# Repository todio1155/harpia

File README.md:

# HARPIA NINHO: introdução

Projeto "Harpia Ninho" é uma impressora 3D projetada para ser open-source (leia a licença atual do projeto antes de usar), durável, modificável e atualmente ficando mais fácil de consertar e fazer módulos de expansão, tipo um LAN/Ethernet, mais NTC, driver de passo, FRAM e muito mais. Ele foi feito para ATX-20 ou ATX-24; licença "CERN-OHL-S-2.0".
## contexto
Eu queria uma impressora 3D barata, eficiente, personalizada e open-source que pudesse ser muito modificada. 

## pré requisitos
[kicad 10.0 ou maior](https://www.kicad.org/download/)

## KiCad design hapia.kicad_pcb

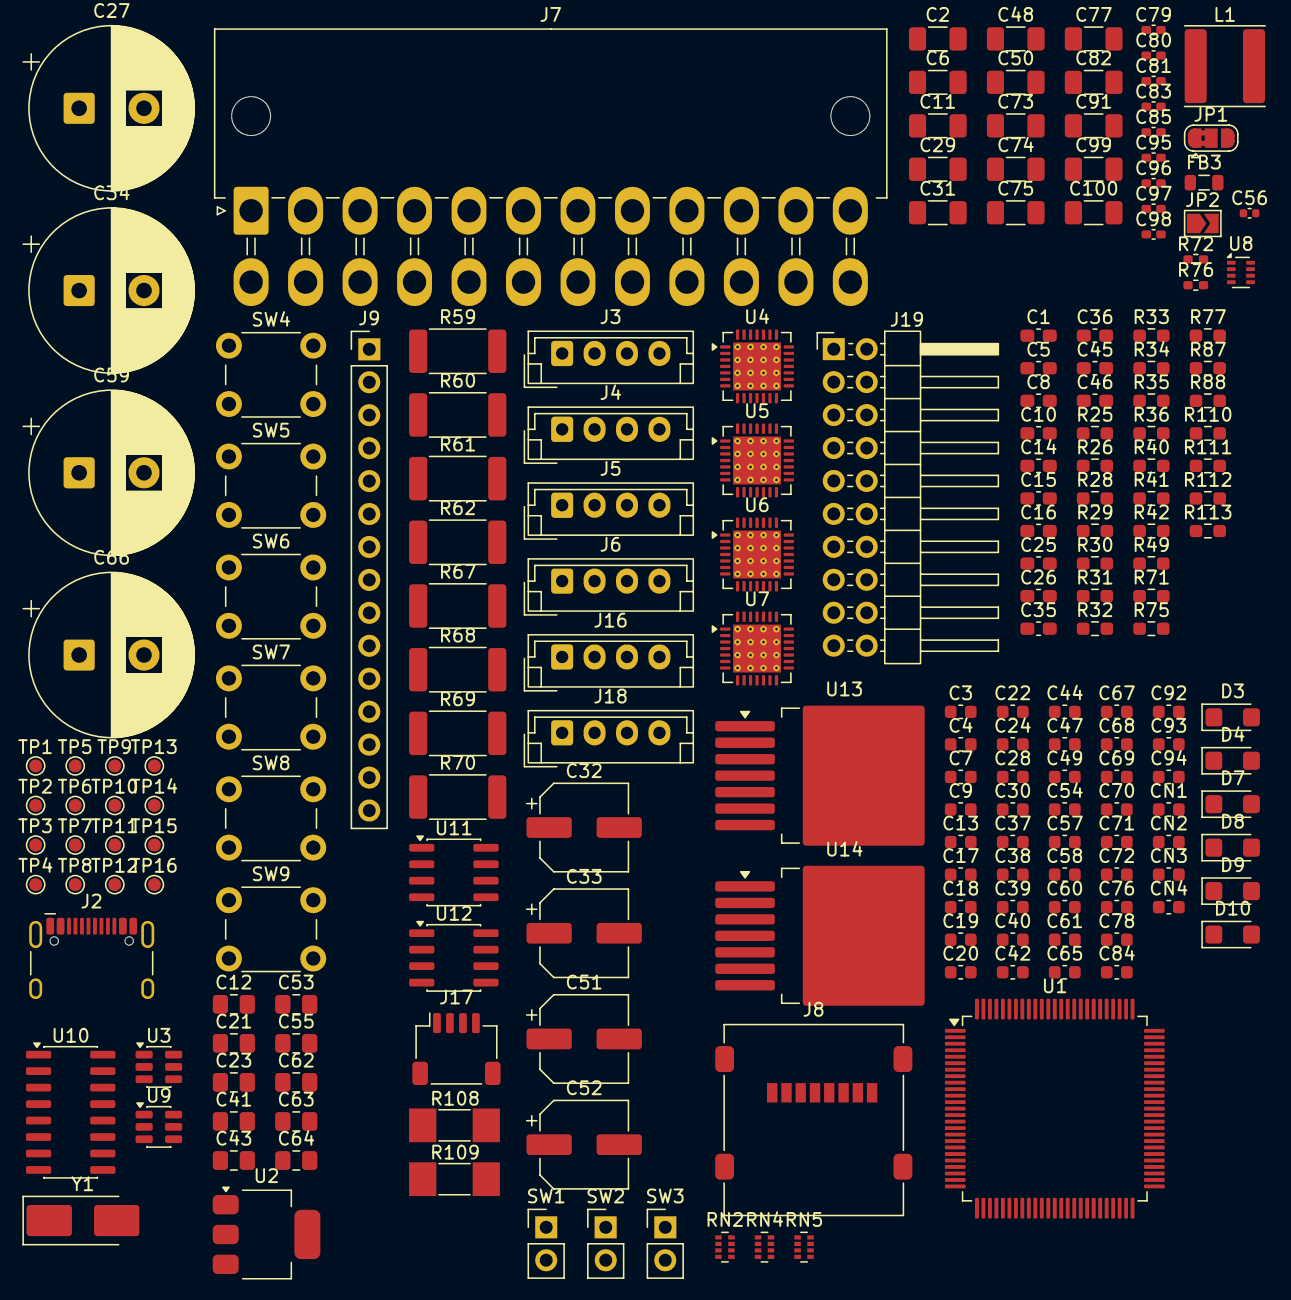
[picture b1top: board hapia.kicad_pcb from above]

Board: 6 copper layers, 200 parts (0 on the bottom side), 149 nets, no tracks yet.

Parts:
C1, C5: 22pf; C_0603_1608Metric_Pad1.08x0.95mm_HandSolder
C2, C6, C11, C29, C31, C48, C50, C73, C74, C75, C77, C82, C91, C99, C100: 10µf; C_1206_3216Metric_Pad1.33x1.80mm_HandSolder
C3, C4, C7, C9, C13, C17, C18, C19, C20, C22, C24, C28, C30, C37, C38, C39, C40, C42, C44, C47, C49, C54, C57, C58, C60, C61, C65, C67, C68, C69, C70, C71, C72, C76, C78, C84, C92, C93, C94: 100nf; C_0603_1608Metric
C8, C10, C14, C25, C26, C45, C46: 4.7µf; C_0603_1608Metric_Pad1.08x0.95mm_HandSolder
C12, C21, C23, C41, C43, C63: 1µf; C_0805_2012Metric_Pad1.18x1.45mm_HandSolder
C15, C16, C35, C36: 22nf; C_0603_1608Metric_Pad1.08x0.95mm_HandSolder
C27, C34, C59, C66: 1000µf; CP_Radial_D12.5mm_P5.00mm
C32, C33, C51, C52: 100µf; CP_Elec_6.3x7.7
C53, C55, C62, C64: 22µf; C_0805_2012Metric_Pad1.18x1.45mm_HandSolder
C56: 33nf; C_0402_1005Metric
C79, C80, C81, C83, C85, C95, C96, C97, C98: 10nf; C_0402_1005Metric_Pad0.74x0.62mm_HandSolder
CN1, CN2, CN3, CN4: 100nf; C_0603_1608Metric
D3: SMF5V0A; D_SMF
D4, D7, D8, D9: SMF3.3; D_SMF
D10: SMF12A; D_SMF
FB3: FerriteBead; L_0805_2012Metric
J2: USB_C_Receptacle_USB2.0_16P; USB_C_Receptacle_HCTL_HC-TYPE-C-16P-01A
J3, J4, J5, J6, J16, J18: Conn_01x04_Pin; JST_EH_B4B-EH-A_1x04_P2.50mm_Vertical
J7: ATX-24; Molex_Mini-Fit_Jr_5569-24A2_2x12_P4.20mm_Horizontal
J8: Micro_SD_Card; microSD_HC_Molex_47219-2001
J9: Conn_01x15_Pin; PinHeader_1x15_P2.54mm_Vertical
J17: Conn_01x04_MountingPin; JST_SH_SM04B-SRSS-TB_1x04-1MP_P1.00mm_Horizontal
J19: ETH; PinHeader_2x10_P2.54mm_Horizontal
JP1: usb/atx; SolderJumper-3_P1.3mm_Bridged2Bar12_RoundedPad1.0x1.5mm
JP2: fre; SolderJumper-2_P1.3mm_Open_TrianglePad1.0x1.5mm
L1: 4.7µh; L_Changjiang_FNR6020S
R25, R26: 22Ω; R_0603_1608Metric_Pad0.98x0.95mm_HandSolder
R28, R29, R30, R31, R32, R33, R34, R35, R36, R40, R41, R42, R49, R75, R110, R111, R112, R113: 33Ω; R_0603_1608Metric_Pad0.98x0.95mm_HandSolder
R59, R60, R61, R62, R67, R68, R69, R70: 100mΩ; R_2512_6332Metric_Pad1.40x3.35mm_HandSolder
R71: 100kΩ; R_0603_1608Metric_Pad0.98x0.95mm_HandSolder
R72: 57.6kΩ; R_0402_1005Metric_Pad0.72x0.64mm_HandSolder
R76: 330Ω; R_0402_1005Metric_Pad0.72x0.64mm_HandSolder
R77: 30.9kΩ; R_0603_1608Metric_Pad0.98x0.95mm_HandSolder
R87, R88: 4.7kΩ; R_0603_1608Metric_Pad0.98x0.95mm_HandSolder
R108, R109: 12Ω; R_MELF_MMB-0207
RN2, RN4, RN5: 33Ω; R_Array_Concave_4x0402
SW1, SW2, SW3: SW_Push; PinHeader_1x02_P2.54mm_Vertical
SW4, SW5, SW6, SW7, SW8, SW9: SW_P; SW_PUSH_6mm_H5mm
TP1, TP2, TP4, TP13: TestPoint; TestPoint_Pad_D1.0mm
TP3, TP16: 3.3v; TestPoint_Pad_D1.0mm
TP5, TP6, TP9, TP10: 3.3v_power; TestPoint_Pad_D1.0mm
TP7, TP8, TP11, TP12: 12v_power; TestPoint_Pad_D1.0mm
TP14: 12v; TestPoint_Pad_D1.0mm
TP15: 5v; TestPoint_Pad_D1.0mm
U1: STM32F407VET6; LQFP-100_14x14mm_P0.5mm
U2: AMS1117-3.3; SOT-223-3_TabPin2
U3, U9: SRV05-4HTG-D; SOT-23-6
U4, U5, U6, U7: TMC2209-LA; VQFN-28-1EP_5x5mm_P0.5mm_EP3.7x3.7mm_ThermalVias
U8: TPS62933F; SOT-583-8
U10: 74HC4051; SOIC-16_3.9x9.9mm_P1.27mm
U11, U12: UCC27524DR; SOIC-8_3.9x4.9mm_P1.27mm
U13, U14: IRFS7530TRL7PP; TO-263-7_TabPin4
Y1: 8mhz; Crystal_SMD_5032-2Pin_5.0x3.2mm_HandSoldering

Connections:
3.3v/1: C2.1, CN1.1 (common), CN1.2 (C1), CN2.2 (C1), JP1.2 (C), TP3.1 (1_1), U1.6 (VBAT), U1.11 (VDD), U1.19 (VDD), U1.28 (VDD), U1.50 (VDD), U1.75 (VDD), U1.100 (VDD)
+3.3V: C61.1, C62.1, C64.1, C70.1, C73.1, C76.1, C77.1, C78.1, C82.1, C91.1, C92.2, D4.1 (A1), J8.4 (VDD), J16.1, J17.1, J18.1, JP1.3 (B), L1.2, R76.1, R87.1, R88.1, SW4.2, SW5.2, SW6.2, SW7.2, SW8.2, SW9.2, TP16.1 (1_1), U9.2 (VN), U10.16 (VCC), U11.6 (V_{DD}), U12.6 (V_{DD})
+3.3Vdev: C12.1, D9.1 (A1), JP1.1 (A), U2.2 (VO)
+3V3: C13.1, C14.1, C19.2, C20.2, C21.2, C23.2, C38.2, C40.2, C41.2, C43.2, TP5.1 (1_1), TP6.1 (1_1), TP9.1 (1_1), TP10.1 (1_1), U4.15 (VCC_IO), U5.9 (MS1/AD0), U5.15 (VCC_IO), U6.10 (MS2/AD1), U6.15 (VCC_IO), U7.9 (MS1/AD0), U7.10 (MS2/AD1), U7.15 (VCC_IO)
+5V: C60.1, C63.1, C71.1, C74.1, J9.13, TP15.1 (1_1)
+5VSB: C57.1, FB3.2, J9.2
+5Vusb: C11.1, U2.3 (VI)
+12P: C18.1, C28.2, C29.2, C30.2, C31.2, C32.1, C33.1, C47.2, C48.2, C49.2, C50.2, C51.1, C52.1, TP7.1 (1_1), TP8.1 (1_1), TP11.1 (1_1), TP12.1 (1_1), U4.22 (VS), U4.28 (VS), U5.22 (VS), U5.28 (VS), U6.22 (VS), U6.28 (VS), U7.22 (VS), U7.28 (VS)
+12V: C27.1, C34.1, C59.1, C65.1, C66.1, C67.1, C68.1, C69.1, C72.1, C75.1, D10.1 (A1), J9.15, TP14.1 (1_1), U11.2 (INA), U11.4 (INB), U12.2 (INA), U12.4 (INB)
/RMII_expansão/vcc_RMII: C99.1, C100.1, CN3.1 (common), CN3.2 (C1), D7.1 (A1)
ATX_PWR_o: D8.1 (A1), U1.97 (PE0)
CLK_0: C1.1, U1.12 (PH0), Y1.2
CLK_X: C5.1, U1.13 (PH1), Y1.1
Fan_1: U1.46 (PE15), U11.1 (ENA)
Fan_2: U1.43 (PE12), U11.8 (ENB)
GND: C1.2, C2.2, C3.2, C4.2, C5.2, C6.2, C7.2, C8.2, C9.2, C10.2, C11.2, C12.2, C13.2, C14.2, C17.1, C19.1, C20.1, C21.1, C22.1, C23.1, C24.1, C25.1, C26.1, C27.2, C28.1, C29.1, C30.1, C31.1, C32.2, C33.2, C34.2, C37.1, C38.1, C39.1, C40.1, C41.1, C42.1, C43.1, C44.1, C45.1, C46.1, C47.1, C48.1, C49.1, C50.1, C51.2, C52.2, C53.2, C54.2, C55.2, C56.2, C57.2, C59.2, C60.2, C61.2, C62.2, C63.2, C64.2, C65.2, C66.2, C67.2, C70.2, C71.2, C72.2, C73.2, C74.2, C75.2, C76.2, C77.2, C78.2, C79.2, C80.2, C81.2, C82.2, C83.2, C84.2, C85.2, C91.2, C92.1, C93.2, C94.2, C95.2, C96.2, C97.2, C98.2, C99.2, C100.2, D3.2 (A2), D4.2 (A2), D7.2 (A2), D8.2 (A2), D9.2 (A2), D10.2 (A2), J2.A1 (GND), J2.A12 (GND), J2.B1 (GND), J2.B12 (GND), J7.3 (GND), J7.5 (GND), J7.7 (GND), J7.15 (GND), J7.17 (GND), J7.18 (GND), J7.19 (GND), J7.24 (GND), J9.1, J9.3, J9.12, J16.2, J17.2, J17.MP (MountPin), J18.2, JP2.1 (A), R59.2, R60.2, R61.2, R62.2, R67.2, R68.2, R69.2, R70.2, R72.2, SW1.1, SW2.1, SW3.2, U1.10 (VSS), U1.20 (VSSA), U1.27 (VSS), U1.74 (VSS), U1.99 (VSS), U2.1 (GND), U3.5 (VP), U4.3 (GND), U4.9 (MS1/AD0), U4.10 (MS2/AD1), U4.13 (CLK), U4.18 (GND), U4.20 (STDBY), U4.29 (GND), U5.3 (GND), U5.10 (MS2/AD1), U5.13 (CLK), U5.18 (GND), U5.20 (STDBY), U5.29 (GND), U6.3 (GND), U6.9 (MS1/AD0), U6.13 (CLK), U6.18 (GND), U6.20 (STDBY), U6.29 (GND), U7.3 (GND), U7.13 (CLK), U7.18 (GND), U7.20 (STDBY), U7.29 (GND), U8.4 (GND), U9.5 (VP), U10.7 (VEE), U10.8 (GND), U11.3 (GND), U12.3 (GND), U13.2 (S), U13.3 (S), U13.5 (S), U13.6 (S), U13.7 (S), U14.2 (S), U14.3 (S), U14.5 (S), U14.6 (S), U14.7 (S)
MUX_EN: U1.98 (PE1), U10.6 (~E)
NTC_EX: C79.1, U10.13 (A0)
NTC_MUX_0: U1.3 (PE4), U10.11 (S0)
NTC_MUX_1: U1.4 (PE5), U10.10 (S1)
NTC_MUX_2: U1.5 (PE6), U10.9 (S2)
NTC_MUX_out: U1.15 (PC0), U10.3 (A)
NTC_driver_1: C81.1, U10.1 (A4)
NTC_driver_2: C96.1, U10.5 (A5)
NTC_driver_3: C97.1, U10.2 (A6)
NTC_driver_4: C98.1, U10.4 (A7)
NTC_ht: C80.1, U10.14 (A1)
NTC_mosfet_1: C83.1, U10.15 (A2)
NTC_mosfet_2: C95.1, U10.12 (A3)
unnamed: J2.A4 (VBUS), J2.A9 (VBUS), J2.B4 (VBUS), J2.B9 (VBUS), TP4.1 (1_1), U3.2 (VN)
unnamed: D3.1 (A1), FB3.1
unnamed: J7.4 (+5V), J7.6 (+5V), J7.21 (+5V), J7.22 (+5V), J7.23 (+5V)
unnamed: J3.1, U4.1 (OB2)
unnamed: J3.2, U4.26 (OB1)
unnamed: J3.3, U4.21 (OA2)
unnamed: J3.4, U4.24 (OA1)
unnamed: J4.1, U5.1 (OB2)
unnamed: J4.2, U5.26 (OB1)
unnamed: J4.3, U5.21 (OA2)
unnamed: J4.4, U5.24 (OA1)
unnamed: J5.1, U6.1 (OB2)
unnamed: J5.2, U6.26 (OB1)
unnamed: J5.3, U6.21 (OA2)
unnamed: J5.4, U6.24 (OA1)
unnamed: J6.1, U7.1 (OB2)
unnamed: J6.2, U7.26 (OB1)
unnamed: J6.3, U7.21 (OA2)
unnamed: J6.4, U7.24 (OA1)
unnamed: JP2.2 (B), U8.1 (RT)
unnamed: R76.2, R77.1
unnamed: RN5.1 (R1.1), U1.38 (PE7)
unnamed: RN5.2 (R2.1), U1.39 (PE8)
unnamed: RN5.3 (R3.1), U1.40 (PE9)
unnamed: RN5.4 (R4.1), U1.41 (PE10)
unnamed: R49.1, U1.23 (PA0)
unnamed: R75.1, U1.25 (PA2)
unnamed: R110.1, U1.26 (PA3)
unnamed: R111.1, U1.29 (PA4)
unnamed: R112.1, U1.30 (PA5)
unnamed: R113.1, U1.31 (PA6)
unnamed: R40.1, U1.72 (PA13)
unnamed: R41.1, U1.76 (PA14)
unnamed: R32.1, U1.89 (PB3)
unnamed: R33.1, U1.90 (PB4)
unnamed: R36.1, U1.91 (PB5)
unnamed: R29.1, U1.48 (PB11)
unnamed: R30.1, U1.51 (PB12)
unnamed: R31.1, U1.52 (PB13)
unnamed: R34.1, U1.78 (PC10)
unnamed: R35.1, U1.79 (PC11)
unnamed: R28.1, U1.88 (PD7)
unnamed: R25.1, U1.61 (PD14)
unnamed: R26.1, U1.62 (PD15)
unnamed: R42.1, U1.42 (PE11)
unnamed: C7.1, C8.1, U1.49 (VCAP_1)
unnamed: C9.1, C10.1, U1.73 (VCAP_2)
unnamed: C22.2, C25.2, U4.8 (5VOUT)
unnamed: R61.1, U4.23 (BRA)
unnamed: R59.1, U4.27 (BRB)
unnamed: C15.2, U4.5 (CPI)
unnamed: C15.1, U4.4 (CPO)
unnamed: C17.2, U4.6 (VCP)
unnamed: C24.2, C26.2, U5.8 (5VOUT)
unnamed: R62.1, U5.23 (BRA)
unnamed: R60.1, U5.27 (BRB)
unnamed: C16.2, U5.5 (CPI)
unnamed: C16.1, U5.4 (CPO)
unnamed: C18.2, U5.6 (VCP)
unnamed: C42.2, C45.2, U6.8 (5VOUT)
unnamed: R69.1, U6.23 (BRA)
unnamed: R67.1, U6.27 (BRB)
unnamed: C35.2, U6.5 (CPI)
unnamed: C35.1, U6.4 (CPO)
unnamed: C39.2, U6.6 (VCP)
unnamed: C44.2, C46.2, U7.8 (5VOUT)
unnamed: R70.1, U7.23 (BRA)
unnamed: R68.1, U7.27 (BRB)
unnamed: C36.2, U7.5 (CPI)
unnamed: C36.1, U7.4 (CPO)
unnamed: C37.2, U7.6 (VCP)
unnamed: C58.1, U8.6 (BST)
unnamed: R71.2, R72.1, U8.2 (EN)
unnamed: R77.2, U8.8 (FB)
unnamed: C56.1, U8.7 (SS)
unnamed: C58.2, L1.1, U8.5 (SW)
unnamed: C53.1, C54.1, C55.1, R71.1, U8.3 (VIN)
unnamed: R108.1, U12.7 (OUTA)
unnamed: R109.1, U12.5 (OUTB)
unnamed: R108.2, U13.1 (G)
unnamed: R109.2, U14.1 (G)
STM_boot: C4.1, SW2.2, TP1.1 (1_1), U1.94 (BOOT0)
STM_nrst: C3.1, SW1.2, TP2.1 (1_1), U1.14 (NRST)
SUB_1: J7.16 (PS_ON#), SW3.1, TP13.1 (1_1), U1.60 (PD13)
SUB_6: U1.1 (PE2), U1.55 (PD8)
SUB_SCL: R88.2, U1.92 (PB6)
SUB_SDA: R87.2, U1.93 (PB7)
S_1: CN4.1 (common), SW4.1
S_2: CN4.2 (C1), SW6.1
S_3: C93.1, SW8.1
S_6: C94.1, SW9.1
S_SCL: J16.3, J17.3, J18.3
S_SDA: J16.4, J17.4, J18.4
TMC_DIR_1: R75.2, U4.19 (DIR)
TMC_DIR_2: R111.2, U6.19 (DIR)
TMC_DIR_3: R113.2, RN5.7 (R2.2), U5.19 (DIR)
TMC_DIR_4: R42.2, U7.19 (DIR)
TMC_step_1: R110.2, U4.16 (STEP)
TMC_step_2: R112.2, U6.16 (STEP)
TMC_step_3: RN5.6 (R3.2), RN5.8 (R1.2), U5.16 (STEP)
TMC_step_4: RN5.5 (R4.2), U7.16 (STEP)
TMC_uart: R49.2, U4.14 (~PD/UART), U5.14 (~PD/UART), U6.14 (~PD/UART), U7.14 (~PD/UART)
USB_C_D+: J2.A6 (D+), J2.B6 (D+), R26.2, U3.4 (IO3)
USB_C_D-: J2.A7 (D-), J2.B7 (D-), R25.2, U3.6 (IO4)
VDDA: C6.1, C84.1, CN2.1 (common), U1.21 (VREF+), U1.22 (VDDA)
exrtusora: U1.44 (PE13), U12.8 (ENB)
gpi_PD0: J9.11, R34.2
gpi_PD1: J9.10, RN2.1 (R1.1)
gpi_PD2: J9.9, R35.2
gpi_PD3: J9.8, RN2.2 (R2.1)
gpi_PD4: J9.7, RN2.3 (R3.1)
gpi_PD5: J9.6, RN2.4 (R4.1)
gpi_PD6: J9.5, RN2.5 (R5.1)
gpi_PD7: J9.4, RN2.6 (R6.1)
hot_bed: U1.45 (PE14), U12.1 (ENA)
hotbed: J7.10 (+12V), J7.11 (+12V)
sd_SCK: J8.5 (CLK), RN4.5 (R5.1), U9.1 (IO1)
sd_cs: J8.2 (DAT3/CD), RN4.8 (R8.1), U9.6 (IO4)
sd_miso: J8.7 (DAT0), RN4.6 (R6.1), U9.3 (IO2)
sd_mosi: J8.3 (CMD), RN4.7 (R7.1), U9.4 (IO3)

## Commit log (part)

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2026-05-15 Add files via upload
    base
2026-06-01 Add files via upload
    V0,5
2026-06-01 Add files via upload
    V0.55
